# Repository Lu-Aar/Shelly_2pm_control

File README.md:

# Shelly_2pm_control

This piece of code is designed to be run on a ESP32 Super Mini.
It is able to search for a SHELLY 2PM by looking for its MAC address. It can then control certain features of it.

For now it's only able to:
- Raise the shutter
- Stop the shutter
- Close the shutter
- Put the shutter on ventilation when it's stopped

When checking out there is one file missing "config.h". This file must be created after checking out and it should contain the following two items:
```c
#define WIFI_SSID "THE_SSID_TO_CONNECT_TO"
#define WIFI_PASS "THE_PASSWORD_FOR_THAT_SSID"
```

## PCB
The PCB was created in KiCad. It's a free opensource program for creating schematics and PCB's.
https://www.kicad.org/

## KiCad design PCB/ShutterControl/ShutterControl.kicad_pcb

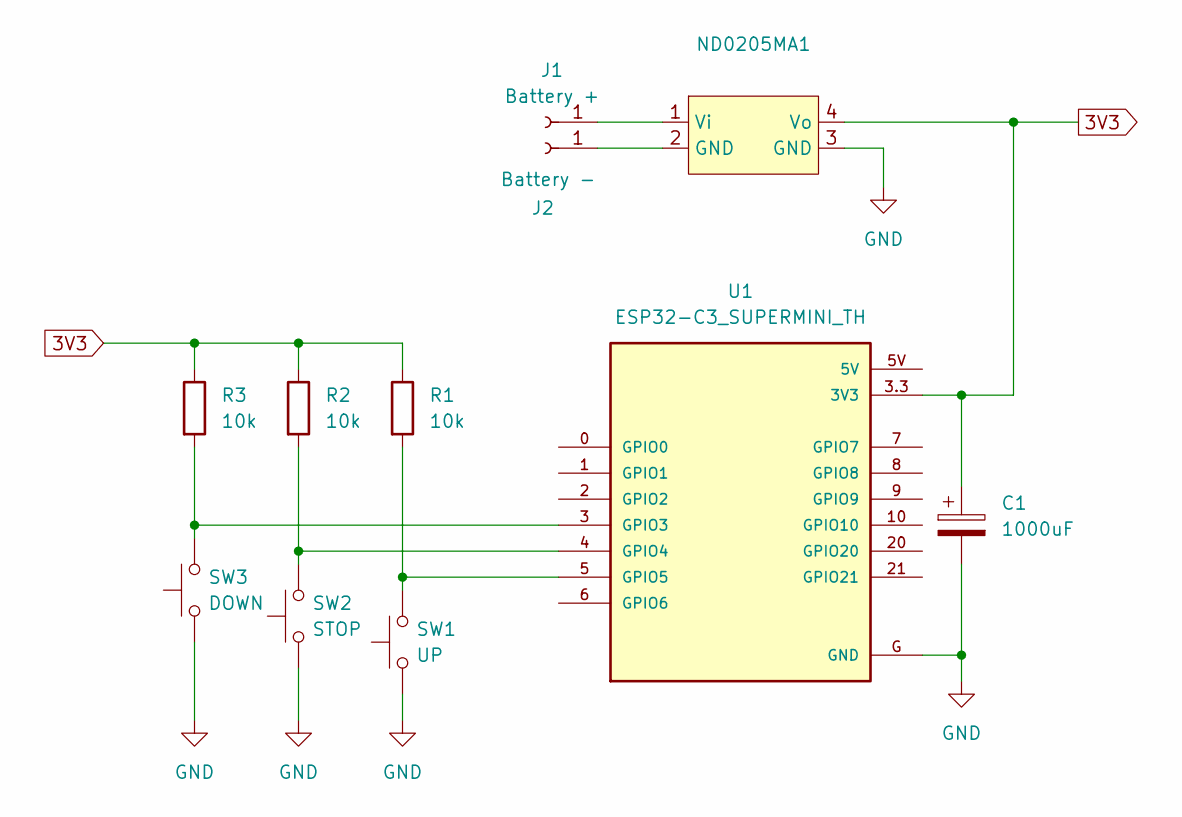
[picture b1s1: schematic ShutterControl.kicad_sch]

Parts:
C1: 1000uF; CP_Radial_D8.0mm_P3.50mm
J1: Battery +; TestPoint_THTPad_2.0x2.0mm_Drill1.0mm
J2: Battery -; TestPoint_THTPad_2.0x2.0mm_Drill1.0mm
ND0205MA1: ND0205MA
R1, R2, R3: 10k; R_Axial_DIN0204_L3.6mm_D1.6mm_P5.08mm_Horizontal
SW1: UP; SW_PUSH_6mm_H5mm
SW2: STOP; SW_PUSH_6mm_H5mm
SW3: DOWN; SW_PUSH_6mm_H5mm
U1: ESP32-C3_SUPERMINI_TH; MODULE_ESP32-C3_SUPERMINI_TH

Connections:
3V3: C1.1, ND0205MA1.4 (Vo), R1.1, R2.1, R3.1, U1.3.3 (3V3); also elsewhere on the board
GND: C1.2, ND0205MA1.3 (GND), SW1.1, SW2.1, SW3.1, U1.G (GND); also elsewhere on the board
unnamed 2: J1.1, ND0205MA1.1 (Vi); also elsewhere on the board
unnamed 3: J2.1, ND0205MA1.2 (GND); also elsewhere on the board
unnamed: R3.2, SW3.2, U1.3 (GPIO3)
unnamed: R2.2, SW2.2, U1.4 (GPIO4)
unnamed: R1.2, SW1.2, U1.5 (GPIO5)

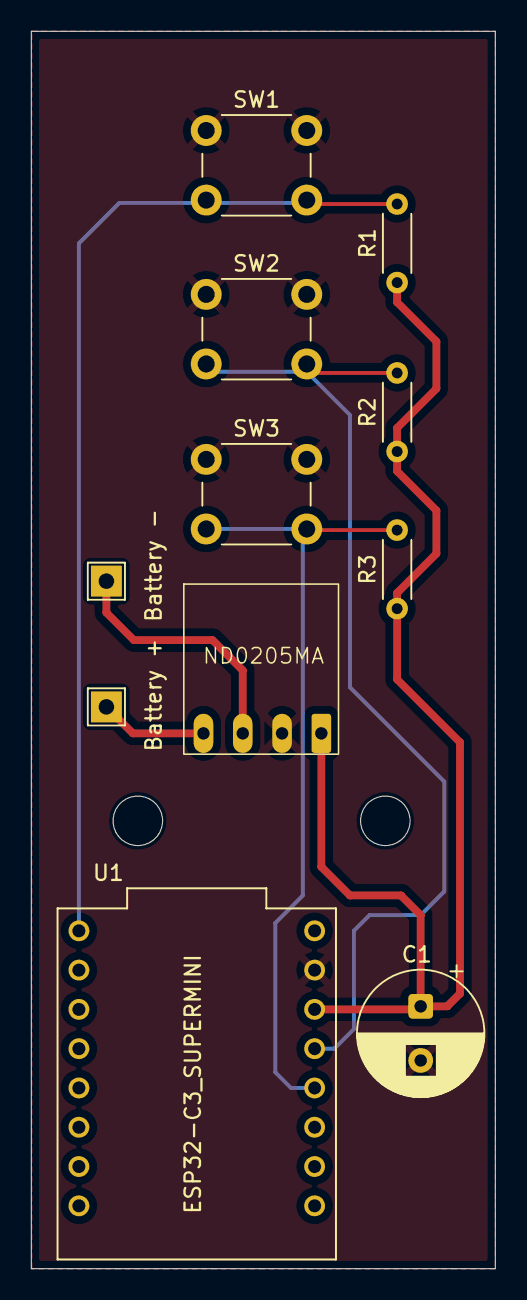
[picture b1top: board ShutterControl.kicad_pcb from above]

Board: 2 copper layers, 30.0 x 80.0 mm, 11 parts (0 on the bottom side), 7 nets.

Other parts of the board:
ND0205MA: ND0205MA

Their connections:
3V3: ND0205MA.4 (Vo); also elsewhere on the board
GND: ND0205MA.3 (GND); also elsewhere on the board
unnamed 2: ND0205MA.1 (Vi); also elsewhere on the board
unnamed 3: ND0205MA.2 (GND); also elsewhere on the board

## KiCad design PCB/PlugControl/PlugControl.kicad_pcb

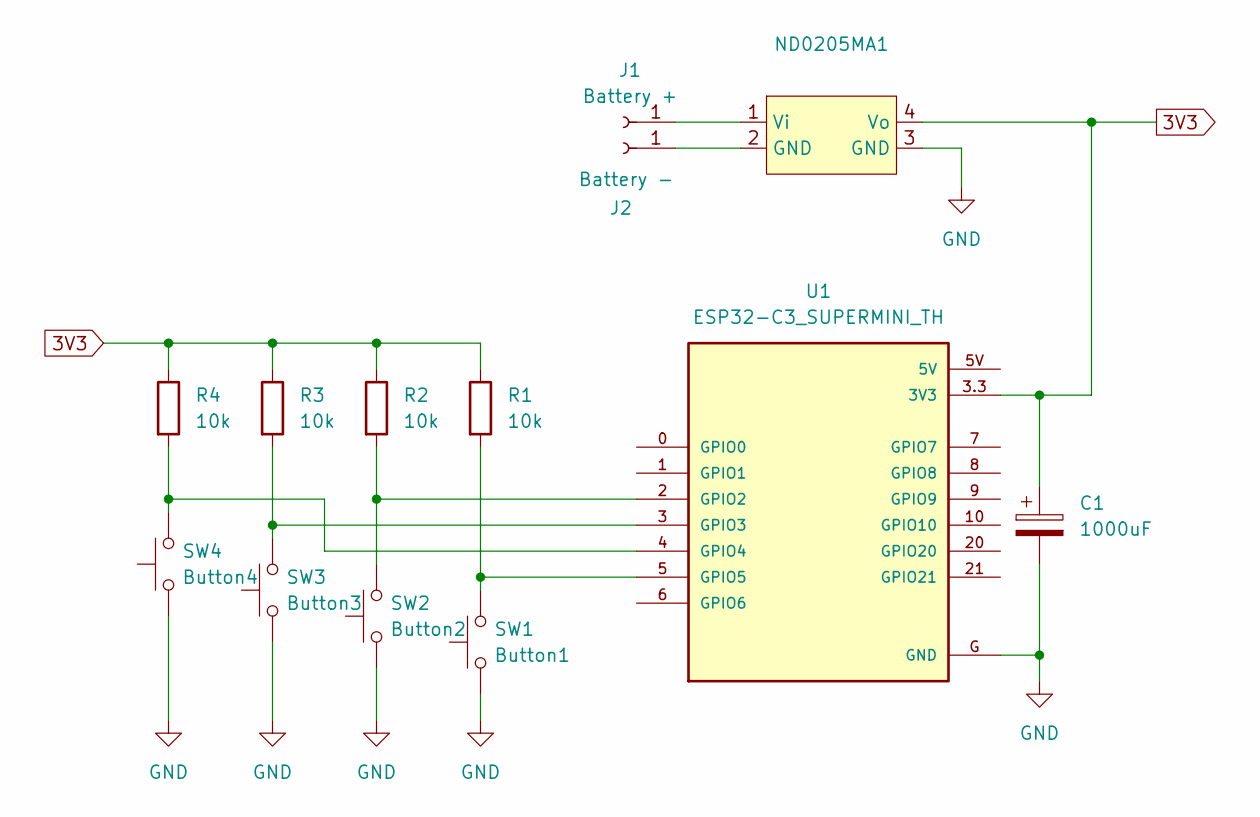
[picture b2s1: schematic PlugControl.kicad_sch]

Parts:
C1: 1000uF; CP_Radial_D8.0mm_P3.50mm
J1: Battery +; TestPoint_THTPad_2.0x2.0mm_Drill1.0mm
J2: Battery -; TestPoint_THTPad_2.0x2.0mm_Drill1.0mm
ND0205MA1: ND0205MA
R1, R2, R3, R4: 10k; R_Axial_DIN0204_L3.6mm_D1.6mm_P5.08mm_Horizontal
SW1: Button1; SW_PUSH_6mm_H5mm
SW2: Button2; SW_PUSH_6mm_H5mm
SW3: Button3; SW_PUSH_6mm_H5mm
SW4: Button4; SW_PUSH_6mm_H5mm
U1: ESP32-C3_SUPERMINI_TH; MODULE_ESP32-C3_SUPERMINI_TH

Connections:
3V3: C1.1, ND0205MA1.4 (Vo), R1.1, R2.1, R3.1, R4.1, U1.3.3 (3V3)
GND: C1.2, ND0205MA1.3 (GND), SW1.1, SW2.1, SW3.1, SW4.1, U1.G (GND)
unnamed: J1.1, ND0205MA1.1 (Vi)
unnamed: J2.1, ND0205MA1.2 (GND)
unnamed: R2.2, SW2.2, U1.2 (GPIO2)
unnamed: R3.2, SW3.2, U1.3 (GPIO3)
unnamed: R4.2, SW4.2, U1.4 (GPIO4)
unnamed: R1.2, SW1.2, U1.5 (GPIO5)

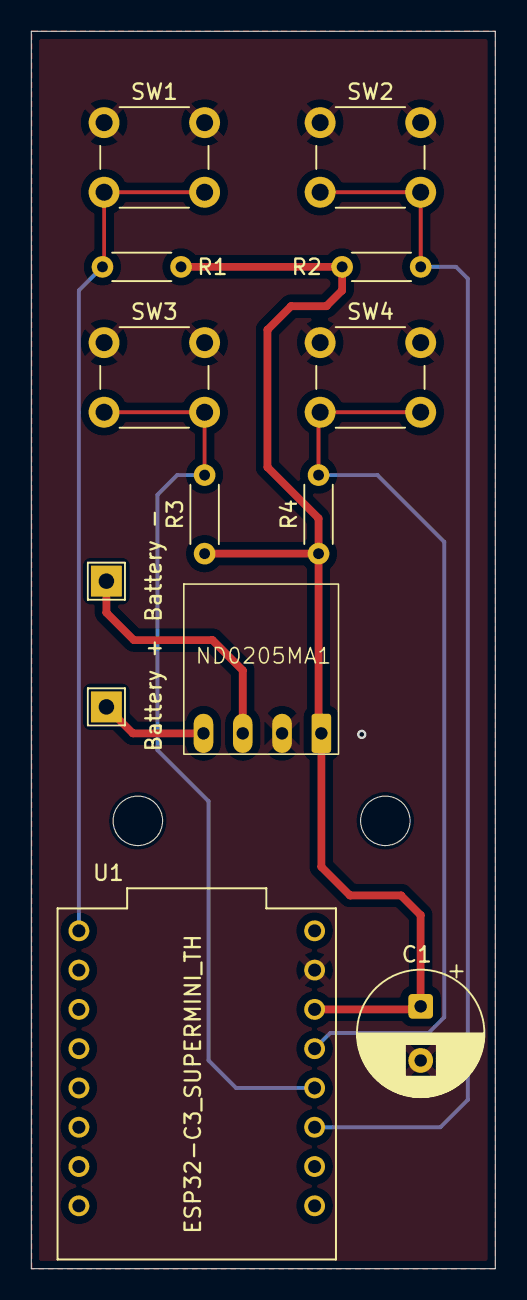
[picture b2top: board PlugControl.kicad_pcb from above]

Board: 2 copper layers, 30.0 x 80.0 mm, 13 parts (0 on the bottom side), 8 nets.

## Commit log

2025-08-15 Created a PCB
2025-08-15 Created a small program to control the Shelly 2pm
2025-08-15 Put the code in the readme in a code block
2025-08-19 Solved an error with committing
2025-08-22 Small update to keep it connected to WiFi
2025-08-24 Changed from light to deep sleep. Can't get the power consumption from the PCB lower than 0.5mA in deep sleep.
